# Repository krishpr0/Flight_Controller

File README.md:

<h1>Flight Controller</h1>

<h5>Flight Controllers developed for Aerial Vehicles</h5>

## Components 
- **STM32F722RET6 MCU**
- **ICM-45686 IMU**
- **BMP580 BARO**
- **QMC5883P MAG**
- **MAX-M10S GPS**
- **3.3V/5V Buck Converters**
- **Micro SD Card Holder**
- **4S LiPO/LiIon**
- **4 Servo/ESCs Pins**

## PCB & Schmeatic Design 
<br>

### Schematic

<br>

### PCB

<br>

### 3D Look of the PCB

### Operation of the Product
- **Firmware** The firmware used for my current setup is the PX4, Which is know for its autonomus reliablity and efficiency.
- You can use BetaFlight, Inav, CleanFlight, Etc... and even a custom firmware!!

- This Flight Controller was made to be able to communicate with Mission Planner, PX4, etc.
- This is one of my finest creation. All of the Pervious versions were either in a Matrix board, or breadboard.

#### Reasons for making it,
- **Reason**, Firstly the reasons I started into Flight Controllers were because of Drones, I always wanted to know how it worked, how it operated, how it functions, and after looking at articles after articles, I got to know Flight Controller was the most important part for a drone to function. So i started looking at Flight Controllers, Many ppl bought pre-made Flight Controllers such as SpeedyBee, Pixhawk, etc. But those lacked features, altho the features they have are the best of the best, their circuits, But i wanted to have as much features as possible, and as well as work my way up the Flight Controllers, This Flight Controllers will be my first ever PCB made with this much functionality.

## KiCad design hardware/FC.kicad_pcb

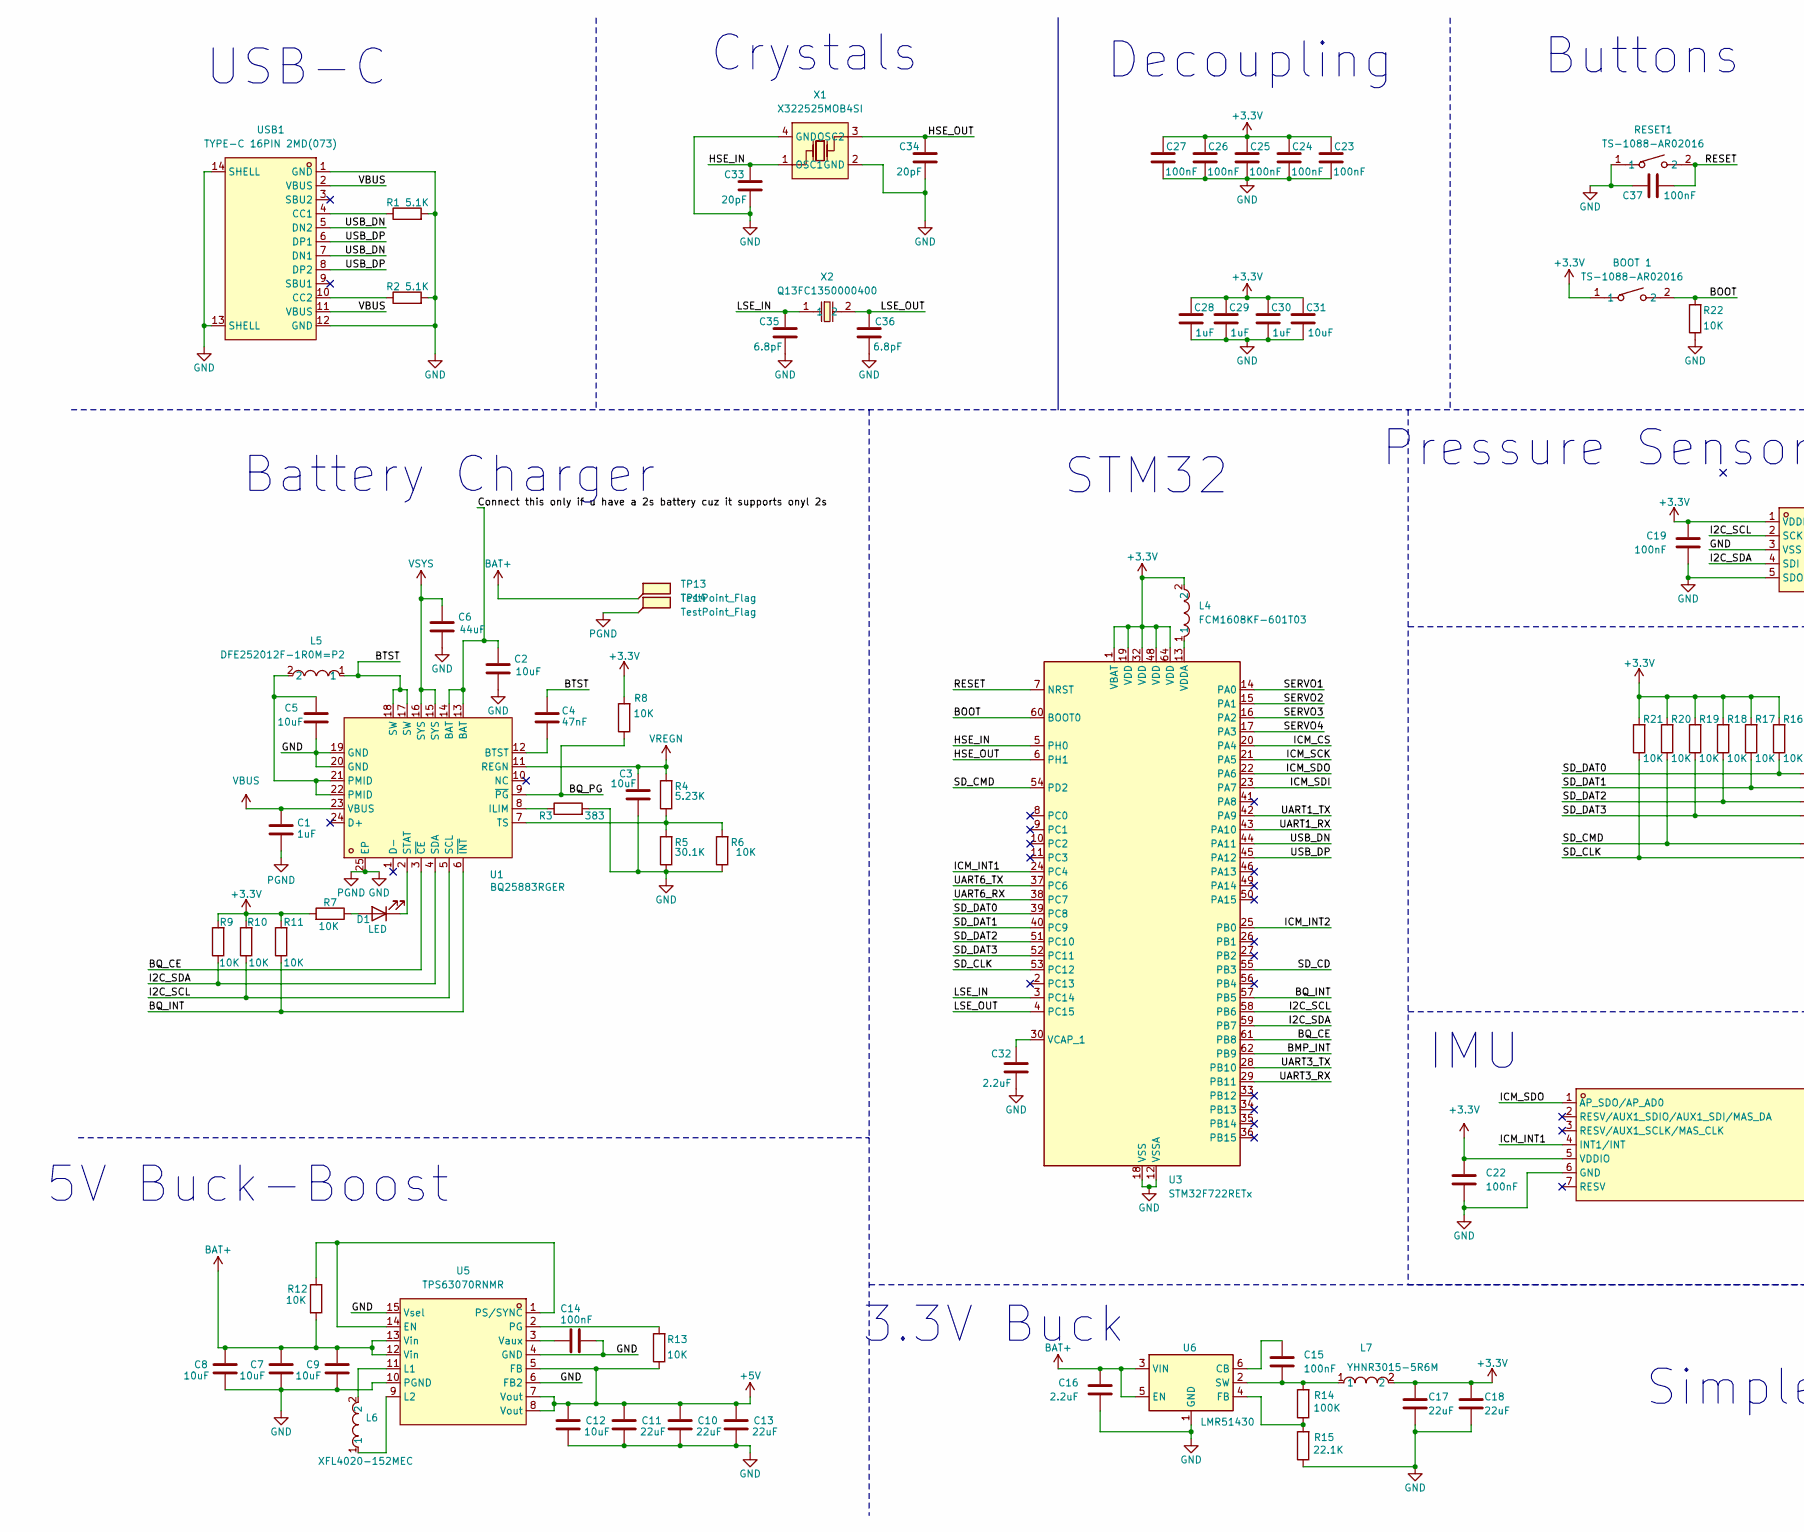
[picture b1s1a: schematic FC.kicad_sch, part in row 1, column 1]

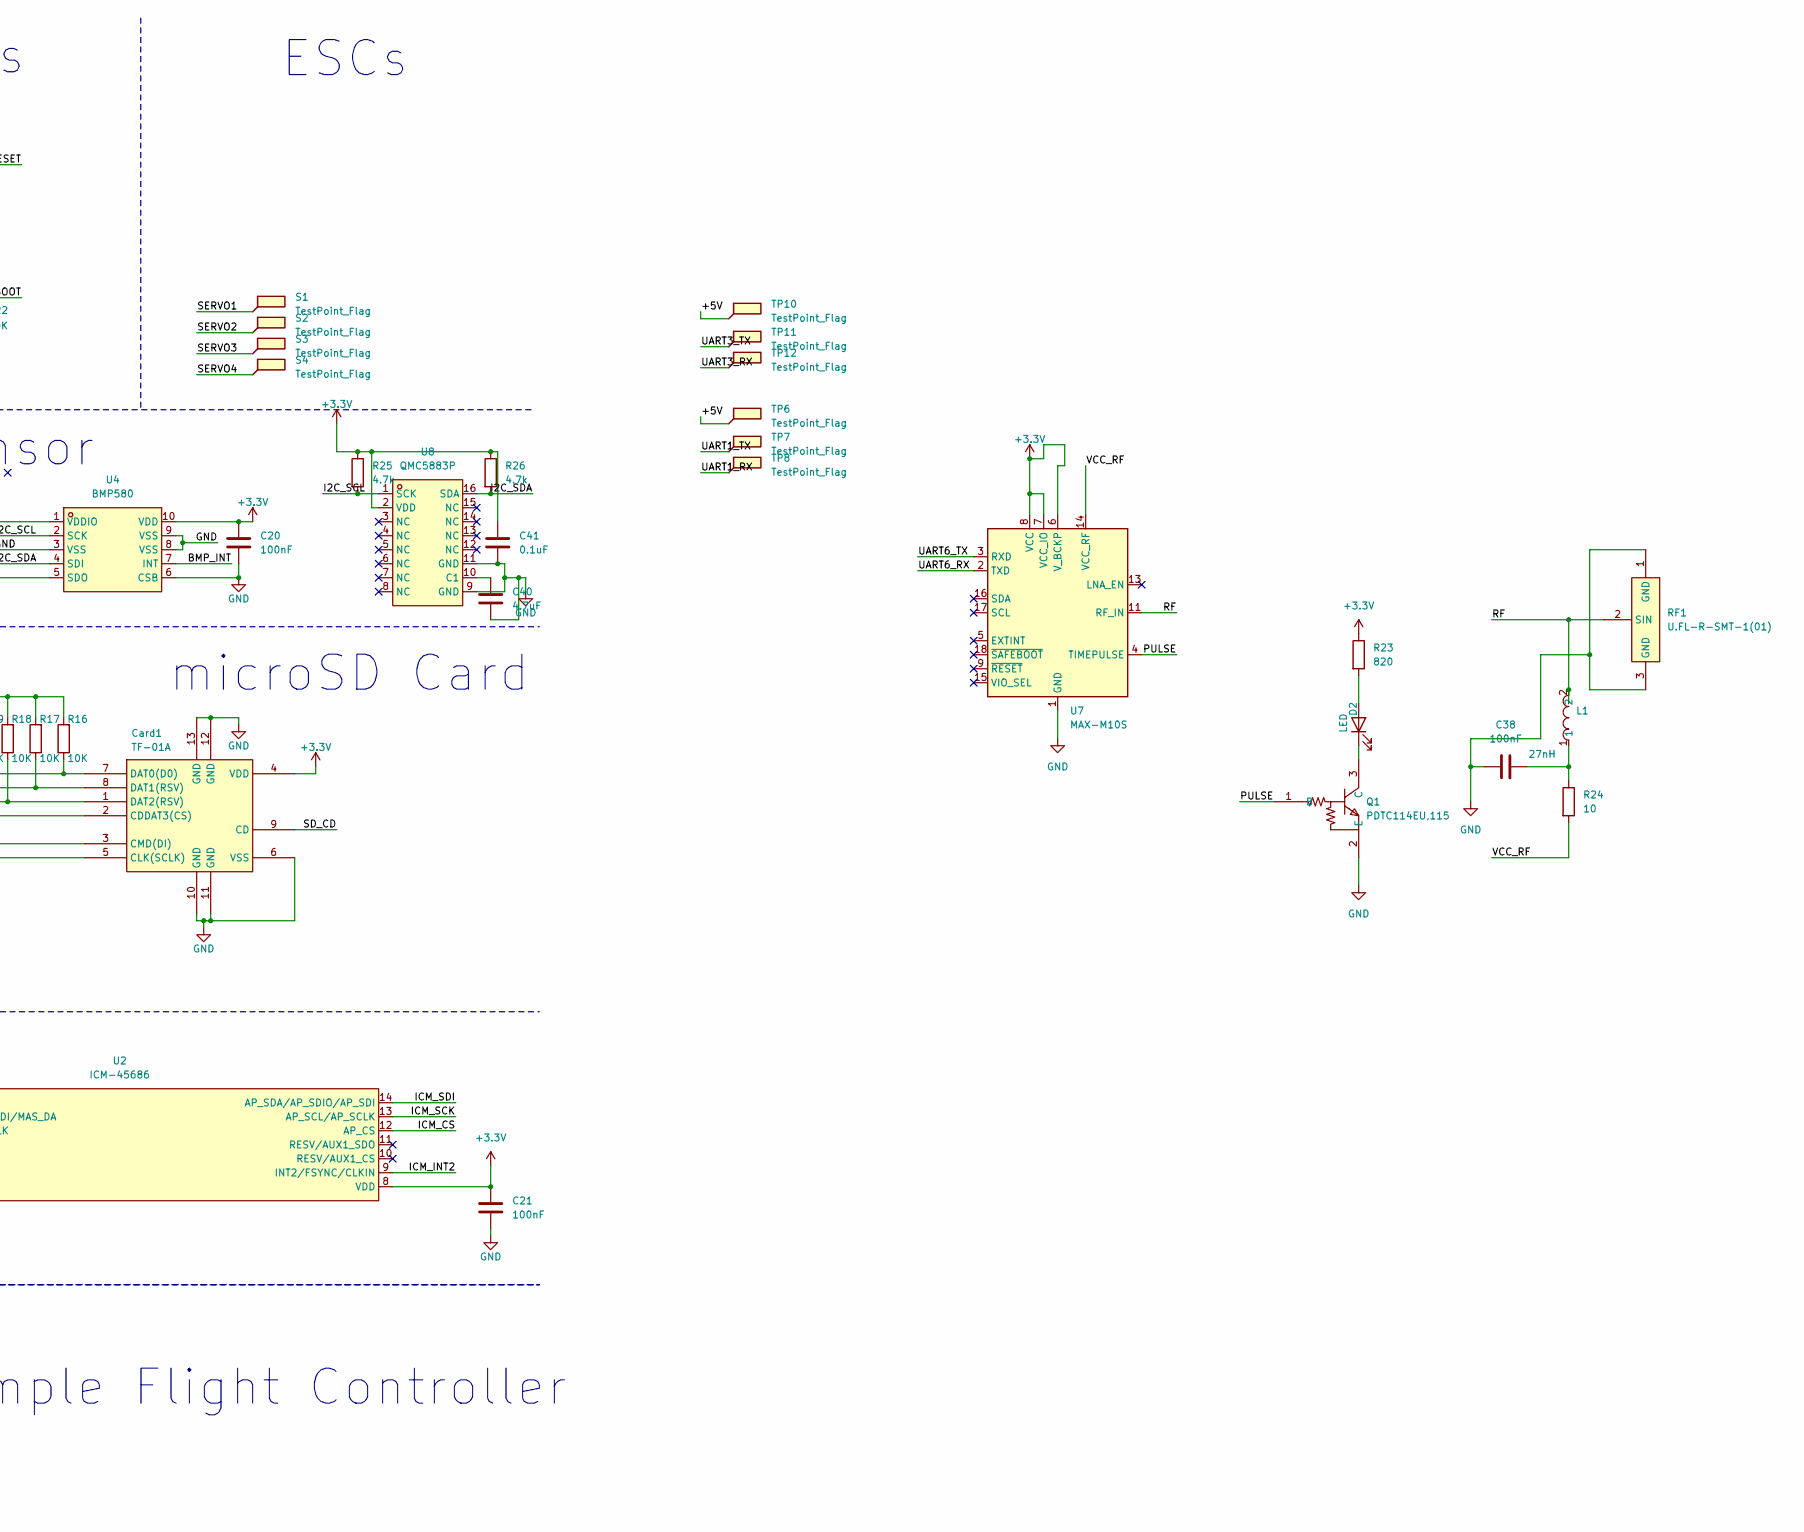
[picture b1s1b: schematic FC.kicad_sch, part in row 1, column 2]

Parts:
BOOT 1: TS-1088-AR02016; SW-SMD_L3.9-W3.0-P4.45; LCSC Part C720477
C1, C28, C29, C30: 1uF; C_0402_1005Metric
C2, C9, C12: 10uF; C_0603_1608Metric
C3, C5, C31: 10uF; C_0402_1005Metric
C4: 47nF; C_0201_0603Metric
C6: 44uF; C_0603_1608Metric
C7, C8: 10uF; C_0805_2012Metric
C10, C11, C13: 22uF; C_0805_2012Metric
C14, C15, C19, C20, C21, C22, C23, C24, C25, C26, C27, C37, C38: 100nF; C_0201_0603Metric
C16: 2.2uF; C_0603_1608Metric
C17, C18: 22uF; C_0402_1005Metric
C32: 2.2uF; C_0201_0603Metric
C33, C34: 20pF; C_0201_0603Metric
C35, C36: 6.8pF; C_0201_0603Metric
C40: 4.7uF; C_0402_1005Metric
C41: 0.1uF; C_0402_1005Metric
Card1: TF-01A; TF-SMD_TF-01A; LCSC Part C91145
D1, D2: LED; LED_0402_1005Metric
L1: 27nH; IND-SMD_L4.0-W4.0-A; LCSC Part C3033018
L4: FCM1608KF-601T03; L0603; LCSC Part C141723
L5: DFE252012F-1R0M=P2; L2520; LCSC Part C435392
L6: XFL4020-152MEC; IND-SMD_L4.0-W4.0-A; LCSC Part C3033018
L7: YHNR3015-5R6M; IND-SMD_L3.0-W3.0; LCSC Part C18236327
Q1: PDTC114EU,115; SOT-323-3_L2.0-W1.3-P1.30-LS2.1-BR; LCSC Part C135830
R1, R2: 5.1K; R_0201_0603Metric
R3: 383; R_0201_0603Metric
R4: 5.23K; R_0201_0603Metric
R5: 30.1K; R_0201_0603Metric
R6, R7, R8, R9, R10, R11, R12, R13, R16, R17, R18, R19, R20, R21, R22: 10K; R_0201_0603Metric
R14: 100K; R_0402_1005Metric
R15: 22.1K; R_0402_1005Metric
R23: 820; R_0201_0603Metric
R24: 10; R_0201_0603Metric
R25, R26: 4.7k; R_0201_0603Metric
RESET1: TS-1088-AR02016; SW-SMD_L3.9-W3.0-P4.45; LCSC Part C720477
RF1: U.FL-R-SMT-1(01); RF-SMD_U.FL-R-SMT-1-80; LCSC Part C598199
S1, S2, S3, S4: TestPoint_Flag; TestPoint_Keystone_5015_Micro_Mini
TP6, TP7, TP8, TP10, TP11, TP12, TP13, TP14: TestPoint_Flag; TestPoint_Keystone_5019_Miniature
U1: BQ25883RGER; VFQFPN-24_L4.0-W4.0-P0.50-BL-EP2.8; LCSC Part C544362
U2: ICM-45686; LGA-14_L3.0-W2.5-P0.50-TL; LCSC Part C22459454
U3: STM32F722RETx; LQFP-64_10x10mm_P0.5mm
U4: BMP580; LGA-10_L2.0-W2.0-P0.50-TL_BMP580; LCSC Part C22391138
U5: TPS63070RNMR; VQFN-HR-15_L3.0-W2.5-P0.50-BL_TPS63070RNMR; LCSC Part C109322
U6: LMR51430; SOT-23-6
U7: MAX-M10S; ublox_MAX
U8: QMC5883P; LGA-16_L3.0-W3.0-P0.50-BL_SQ; LCSC Part C2847467
USB1: TYPE-C 16PIN 2MD(073); USB-C-SMD_TYPE-C-6PIN-2MD-073; LCSC Part C2765186
X1: X322525MOB4SI; CRYSTAL-SMD_4P-L3.2-W2.5-BL; LCSC Part C9006
X2: Q13FC1350000400; FC-135R_L3.2-W1.5; LCSC Part C32346

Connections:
+3.3V: BOOT 1.1, C17.1, C18.1, C19.1, C20.1, C21.1, C22.1, C23.1, C24.1, C25.1, C26.1, C27.1, C28.1, C29.1, C30.1, C31.1, C41.1, Card1.4 (VDD), L4.2, L7.2, R7.2, R8.2, R9.2, R10.2, R11.2, R16.2, R17.2, R18.2, R19.2, R20.2, R21.2, R23.1, R25.1, R26.1, U2.5 (VDDIO), U2.8 (VDD), U3.1 (VBAT), U3.19 (VDD), U3.32 (VDD), U3.48 (VDD), U3.64 (VDD), U4.1 (VDDIO), U4.10 (VDD), U7.6 (V_BCKP), U7.7 (VCC_IO), U7.8 (VCC), U8.2 (VDD)
+5V: C10.1, C11.1, C12.1, C13.1, R13.1, TP6.1, TP10.1, U5.5 (FB), U5.7 (Vout), U5.8 (Vout)
/BMP_INT: U3.62 (PB9), U4.7 (INT)
/BOOT: BOOT 1.2, R22.2, U3.60 (BOOT0)
/BQ_CE: U1.3 (~CE), U3.61 (PB8)
/BQ_INT: R11.1, U1.6 (~INT), U3.57 (PB5)
/BQ_PG: R8.1, U1.9 (~PG)
/BTST: C4.1, L5.1, U1.17 (SW), U1.18 (SW)
/Connect this only if u have a 2s battery cuz it supports onyl 2s: C2.1, U1.13 (BAT), U1.14 (BAT)
/HSE_IN: C33.1, U3.5 (PH0), X1.1 (OSC1)
/HSE_OUT: C34.1, U3.6 (PH1), X1.3 (OSC2)
/I2C_SCL: R10.1, R25.2, U1.5 (SCL), U3.58 (PB6), U4.2 (SCK), U8.1 (SCK)
/I2C_SDA: R9.1, R26.2, U1.4 (SDA), U3.59 (PB7), U4.4 (SDI), U8.16 (SDA)
/ICM_CS: U2.12 (AP_CS), U3.20 (PA4)
/ICM_INT1: U2.4 (INT1/INT), U3.24 (PC4)
/ICM_INT2: U2.9 (INT2/FSYNC/CLKIN), U3.25 (PB0)
/ICM_SCK: U2.13 (AP_SCL/AP_SCLK), U3.21 (PA5)
/ICM_SDI: U2.14 (AP_SDA/AP_SDIO/AP_SDI), U3.23 (PA7)
/ICM_SDO: U2.1 (AP_SDO/AP_AD0), U3.22 (PA6)
/LSE_IN: C35.1, U3.3 (PC14), X2.1
/LSE_OUT: C36.1, U3.4 (PC15), X2.2
/PULSE: Q1.1 (B), U7.4 (TIMEPULSE)
/RESET: C37.2, RESET1.2, U3.7 (NRST)
/RF: L1.2, RF1.2 (SIN), U7.11 (RF_IN)
/SD_CD: Card1.9 (CD), U3.55 (PB3)
/SD_CLK: Card1.5 (CLK(SCLK)), R21.1, U3.53 (PC12)
/SD_CMD: Card1.3 (CMD(DI)), R20.1, U3.54 (PD2)
/SD_DAT0: Card1.7 (DAT0(D0)), R16.1, U3.39 (PC8)
/SD_DAT1: Card1.8 (DAT1(RSV)), R17.1, U3.40 (PC9)
/SD_DAT2: Card1.1 (DAT2(RSV)), R18.1, U3.51 (PC10)
/SD_DAT3: Card1.2 (CDDAT3(CS)), R19.1, U3.52 (PC11)
/SERVO1: S1.1, U3.14 (PA0)
/SERVO2: S2.1, U3.15 (PA1)
/SERVO3: S3.1, U3.16 (PA2)
/SERVO4: S4.1, U3.17 (PA3)
/UART1_RX: TP8.1, U3.43 (PA10)
/UART1_TX: TP7.1, U3.42 (PA9)
/UART3_RX: TP12.1, U3.29 (PB11)
/UART3_TX: TP11.1, U3.28 (PB10)
/UART6_RX: U3.38 (PC7), U7.2 (TXD)
/UART6_TX: U3.37 (PC6), U7.3 (RXD)
/USB_DN: U3.44 (PA11), USB1.5 (DN2), USB1.7 (DN1)
/USB_DP: U3.45 (PA12), USB1.6 (DP1), USB1.8 (DP2)
/VCC_RF: R24.2, U7.14 (VCC_RF)
BAT+: C7.1, C8.1, C9.1, C16.1, R12.2, TP13.1, U5.12 (Vin), U5.13 (Vin), U6.3 (VIN), U6.5 (EN)
GND: C1.2, C2.2, C3.2, C5.2, C6.2, C7.2, C8.2, C9.2, C10.2, C11.2, C12.2, C13.2, C14.2, C16.2, C17.2, C18.2, C19.2, C20.2, C21.2, C22.2, C23.2, C24.2, C25.2, C26.2, C27.2, C28.2, C29.2, C30.2, C31.2, C32.2, C33.2, C34.2, C35.2, C36.2, C37.1, C38.1, C40.2, C41.2, Card1.6 (VSS), Card1.10 (GND), Card1.11 (GND), Card1.12 (GND), Card1.13 (GND), Q1.2 (E), R1.2, R2.2, R3.2, R5.1, R6.1, R15.1, R22.1, RESET1.1, RF1.1 (GND), RF1.3 (GND), TP14.1, U1.19 (GND), U1.20 (GND), U1.25 (EP), U2.6 (GND), U3.12 (VSSA), U3.18 (VSS), U3.31 (VSS), U3.47 (VSS), U3.63 (VSS), U4.3 (VSS), U4.5 (SDO), U4.6 (CSB), U4.8 (VSS), U4.9 (VSS), U5.4 (GND), U5.6 (FB2), U5.10 (PGND), U5.15 (Vsel), U6.1 (GND), U7.1 (GND), U7.10 (GND), U7.12 (GND), U8.9 (GND), U8.11 (GND), USB1.1 (GND), USB1.12 (GND), USB1.13 (SHELL), USB1.14 (SHELL), X1.2 (GND), X1.4 (GND); also elsewhere on the board
unnamed: C5.1, L5.2, U1.21 (PMID), U1.22 (PMID)
unnamed: C38.2, L1.1, R24.1
unnamed: D1.2 (A), R7.1
unnamed: D1.1 (K), U1.2 (STAT)
unnamed: D2.2 (A), R23.2
unnamed: D2.1 (K), Q1.3 (C)
unnamed: C4.2, U1.12 (BTST)
unnamed: R3.1, U1.8 (ILIM)
unnamed: R4.1, R5.2, R6.2, U1.7 (TS)
unnamed: C32.1, U3.30 (VCAP_1)
unnamed: L4.1, U3.13 (VDDA)
unnamed: R12.1, U5.1 (PS/SYNC), U5.14 (EN)
unnamed: L6.2, U5.11 (L1)
unnamed: L6.1, U5.9 (L2)
unnamed: R13.2, U5.2 (PG)
unnamed: C14.1, U5.3 (Vaux)
unnamed: C15.1, U6.6 (CB)
unnamed: R14.1, R15.2, U6.4 (FB)
unnamed: C15.2, L7.1, R14.2, U6.2 (SW)
unnamed: C40.1, U8.10 (C1)
unnamed: R1.1, USB1.4 (CC1)
unnamed: R2.1, USB1.10 (CC2)
VBUS: C1.1, U1.23 (VBUS), USB1.2 (VBUS), USB1.11 (VBUS)
VREGN: C3.1, R4.2, U1.11 (REGN)
VSYS: C6.1, U1.15 (SYS), U1.16 (SYS)

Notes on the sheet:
Simple Flight Controller
Pressure Sensor
Decoupling
3.3V Buck
Buttons
IMU
USB-C
ESCs
Battery Charger
STM32
Crystals
microSD Card
5V Buck-Boost

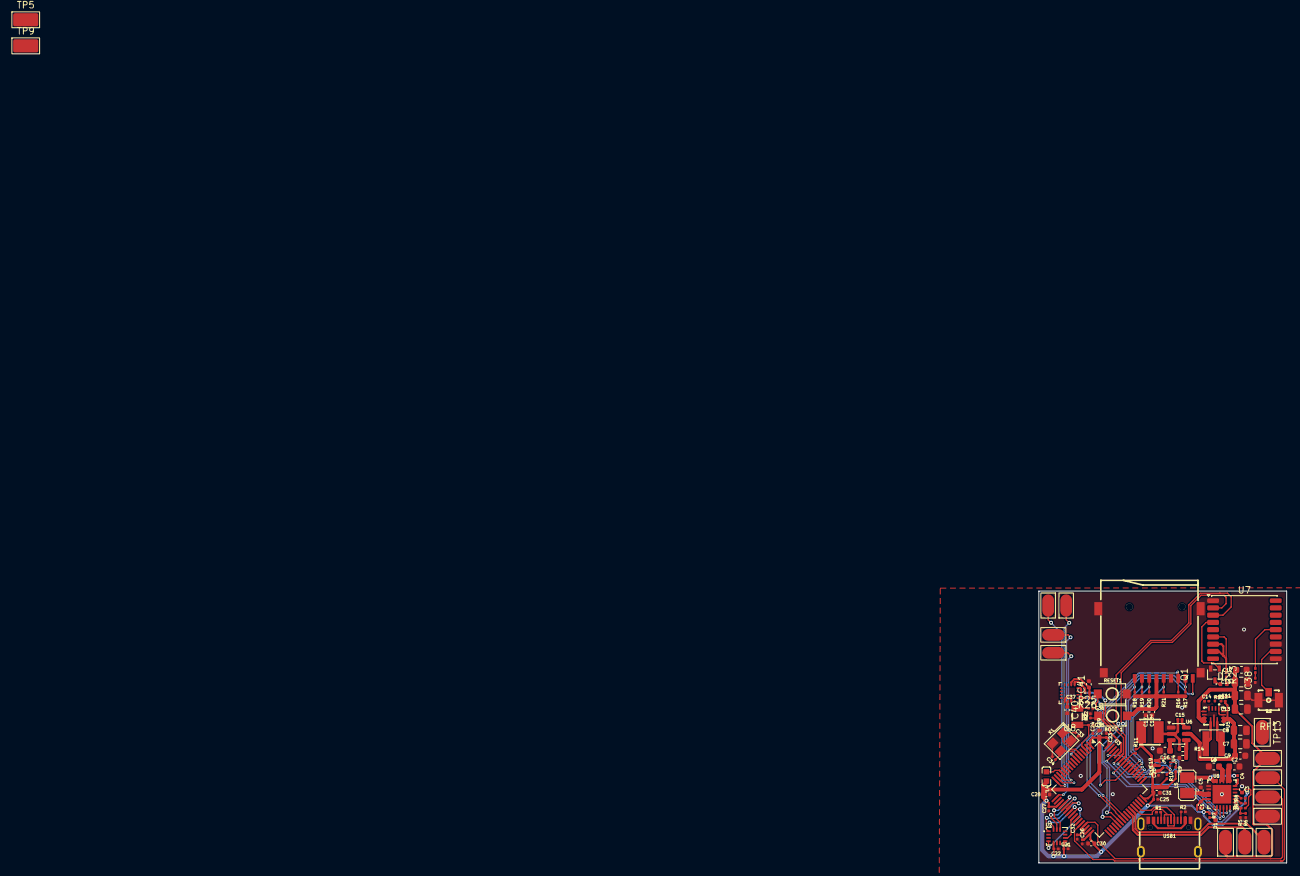
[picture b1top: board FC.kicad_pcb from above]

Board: 2 copper layers, 37.6 x 41.2 mm, 102 parts (0 on the bottom side), 71 nets.

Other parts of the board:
TP5, TP9: TestPoint_Flag; TestPoint_Keystone_5019_Miniature

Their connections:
GND: TP5.1, TP9.1; also elsewhere on the board

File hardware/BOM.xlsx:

No. | Quantity | Comment | Designator | Footprint | Value | Manufacturer Part | Manufacturer | Supplier Part | Supplier
1 | 4 | Test-Point | +5V,GND,U3_RX,U3_TX | Test-Point-0.5mm
2 | 2 | TS-1088-AR02016 | BOOT1,RESET1 | SW-SMD_L3.9-W3.0-P4.45 |  | TS-1088-AR02016 | XUNPU(讯普) | C720477 | LCSC
3 | 5 | Device_C | C7,C8,C9,C12,C31 | C0603 | 10uF
4 | 5 | Device_C | C10,C11,C13,C17,C18 | C0603 | 22uF
5 | 13 | Device_C | C14,C15,C19,C20,C21,C22,C23,C24,C25,C26,C27,C37,C38 | C0603 | 100nF
6 | 2 | Device_C | C16,C32 | C0603 | 2.2uF
7 | 3 | Device_C | C28,C29,C30 | C0603 | 1uF
8 | 2 | Device_C | C33,C34 | C0603 | 20pF
9 | 2 | Device_C | C35,C36 | C0603 | 6.8pF
10 | 1 | Device_C | C40 | C0603 | 4.7uF
11 | 1 | Device_C | C41 | C0603 | 0.1uF
12 | 1 | TF-01A | Card1 | TF-SMD_TF-01A |  | TF-01A | 韩国韩荣 | C91145 | LCSC
13 | 1 | HX PH254-01-04-Z-L11.5 straight pin header | H1 | HDR-TH_4P-HX-PH254-01-04-Z-L11.5 |  | HX PH254-01-04-Z-L11.5 straight pin header | hanxia(韩下) | C52016392 | LCSC
14 | 2 | 1.5uH | L1,L6 | IND-SMD_L4.0-W4.0-A | 1.5uH | XFL4020-152MEC | Coilcraft(线艺) | C3033018 | LCSC
15 | 1 | FCM1608KF-601T03 | L4 | L0603 |  | FCM1608KF-601T03 | TAI-TECH(台庆) | C141723 | LCSC
16 | 1 | 5.6uH | L7 | IND-SMD_L3.0-W3.0 | 5.6uH | YHNR3015-5R6M | YJYCOIN(益嘉源) | C18236327 | LCSC
17 | 1 | LED_0402-R | LED1 | LED0402-RD_YELLOW
18 | 4 | HX PH254-01-03-Z-L11.5 pcb pin header | M1,M2,M3,M4 | HDR-TH_3P-P2.54-V-M-1 |  | HX PH254-01-03-Z-L11.5 pcb pin header | hanxia(韩下) | C52016391 | LCSC
19 | 1 | PDTC114EU,115 | Q1 | SOT-323-3_L2.0-W1.3-P1.30-LS2.1-BR |  | PDTC114EU,115 | Nexperia(安世) | C135830 | LCSC
20 | 2 | Device_R | R1,R2 | C0201 | 5.1K
21 | 9 | Device_R | R12,R13,R16,R17,R18,R19,R20,R21,R22 | C0201 | 10K
22 | 1 | Device_R | R14 | C0201 | 100K
23 | 1 | Device_R | R15 | C0201 | 22.1K
24 | 1 | Device_R | R23 | C0201 | 820
25 | 1 | Device_R | R24 | C0201 | 10
26 | 2 | Device_R | R25,R26 | C0201 | 4.7k
27 | 1 | 6GHz | RF1 | RF-SMD_U.FL-R-SMT-1-80 | 6GHz | U.FL-R-SMT-1(01) | HRS(广濑) | C598199 | LCSC
28 | 1 | ICM-45686 | U2 | LGA-14_L3.0-W2.5-P0.50-TL |  | ICM-45686 | TDK InvenSense(应美盛) | C22459454 | LCSC
29 | 1 | STM32F722RET6 | U3 | LQFP-64_L10.0-W10.0-P0.50-LS12.0-BL |  | STM32F722RET6 | ST(意法半导体) | C118207 | LCSC
30 | 1 | TPS63070RNMR | U5 | VQFN-HR-15_L3.0-W2.5-P0.50-BL_TPS63070RNMR |  | TPS63070RNMR | TI(德州仪器) | C109322 | LCSC
31 | 1 | LMR51430XDDCR | U6 | SOT-23-6_L2.9-W1.6-P0.95-LS2.8-BL |  | LMR51430XDDCR | TI(德州仪器) | C5185863 | LCSC
32 | 1 | MAX-M10S-00B | U7 | SMD-18_L10.1-W9.7-P1.10-TL_SKG09F |  | MAX-M10S-00B | U-BLOX | C4153167 | LCSC
33 | 1 | QMC5883P | U8 | LGA-16_L3.0-W3.0-P0.50-BL_SQ |  | QMC5883P | QST(上海矽睿) | C2847467 | LCSC
34 | 1 | BMP580 | U9 | LGA-10_L2.0-W2.0-P0.50-TL_BMP580 |  | BMP580 | Bosch(博世) | C22391138 | LCSC
35 | 1 | TYPE-C 16PIN 2MD(073) | USB1 | USB-C-SMD_TYPE-C-6PIN-2MD-073 |  | TYPE-C 16PIN 2MD(073) | SHOU HAN(首韩) | C2765186 | LCSC
36 | 1 | 25MHz | X1 | CRYSTAL-SMD_4P-L3.2-W2.5-BL | 25MHz | X322525MOB4SI | YXC(扬兴晶振) | C9006 | LCSC
37 | 1 | 32.768kHz | X2 | OSC-SMD_2P-L3.2-W1.5 | 32.768kHz | ABS07-32.768KHZ-T | ABRACON | C130253 | LCSC

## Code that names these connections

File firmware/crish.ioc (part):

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Mcu.Name=STM32F722R(C-E)Tx
Mcu.Package=LQFP64
Mcu.UserName=STM32F722RETx
PA0-WKUP.Signal=S_TIM2_CH1_ETR
PA1.Signal=S_TIM2_CH2
PA10.Signal=USART1_RX
PA11.Signal=USB_OTG_FS_DM
PA12.Signal=USB_OTG_FS_DP
PA2.Signal=S_TIM2_CH3
PA3.Signal=S_TIM2_CH4
PA4.Signal=SPI1_NSS
PA5.Signal=SPI1_SCK
PA6.Signal=SPI1_MISO
PA7.Signal=SPI1_MOSI
PA9.Signal=USART1_TX
PB0.Signal=GPXTI0
PB10.Signal=USART3_TX
PB11.Signal=USART3_RX
PB3.Signal=GPIO_Input
PB5.Signal=GPXTI5
PB6.Signal=I2C1_SCL
PB7.Signal=I2C1_SDA
PB8.Signal=GPIO_Output
PB9.Signal=GPXTI9
PC10.Signal=SDMMC1_D2
PC11.Signal=SDMMC1_D3
PC12.Signal=SDMMC1_CK
PC14-OSC32_IN.Mode=LSE-External-Oscillator
PC14-OSC32_IN.Signal=RCC_OSC32_IN
PC15-OSC32_OUT.Mode=LSE-External-Oscillator
PC15-OSC32_OUT.Signal=RCC_OSC32_OUT
PC4.Signal=GPXTI4
PC6.Signal=USART6_TX
PC7.Signal=USART6_RX
PC8.Signal=SDMMC1_D0
PC9.Signal=SDMMC1_D1
PD2.Signal=SDMMC1_CMD
PH0-OSC_IN.Mode=HSE-External-Oscillator
PH0-OSC_IN.Signal=RCC_OSC_IN
PH1-OSC_OUT.Mode=HSE-External-Oscillator
PH1-OSC_OUT.Signal=RCC_OSC_OUT
RCC.HSE_VALUE=25000000
board=custom

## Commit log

2025-12-27 Flight Controller
2025-12-27 Added a hole in the PCB for holding it to the FC of mine.
2025-12-27 Added the BOM
2025-12-27 fixed a few errors in the PCB
2025-12-30 trying to add the GPS with the more servo functions and emptying of UARTs ports as much as possible
2026-01-11 Srinked the size of the FC with adding the GPS in progress and also trying to make the FC small as opssible.
2026-01-17 Done
2026-01-17 Doneee
2026-02-10 Finished
